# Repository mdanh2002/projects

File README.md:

# ToughDev Source Code Archive

This repository contains source code, experiments, utilities, and supporting files for projects documented on [ToughDev](https://www.toughdev.com).

I’m Minh Danh, a Singapore-based software engineer working across:

* Embedded Linux and microcontroller firmware
* C, C++, Java, Python, C#, and backend systems
* Virtualization, emulation, and retro computing
* Reverse engineering and hardware integration
* VoIP, networking, and communication systems
* AI-assisted software and data analysis

Featured work includes custom x86 and hardware emulators, QEMU experiments, embedded text-to-speech, radio and audio projects, firmware analysis, device drivers, and integrations with legacy or undocumented hardware.

The code in this repository is provided mainly as a companion to the technical articles on ToughDev. Individual projects may be experimental, hardware-specific, or preserved for reference rather than packaged as production-ready libraries.

## More Information

For project descriptions, schematics, technical investigations, build notes, and related articles, visit:

**https://www.toughdev.com**

You can also view my background and highlighted projects on the [ToughDev About page](https://www.toughdev.com/about).

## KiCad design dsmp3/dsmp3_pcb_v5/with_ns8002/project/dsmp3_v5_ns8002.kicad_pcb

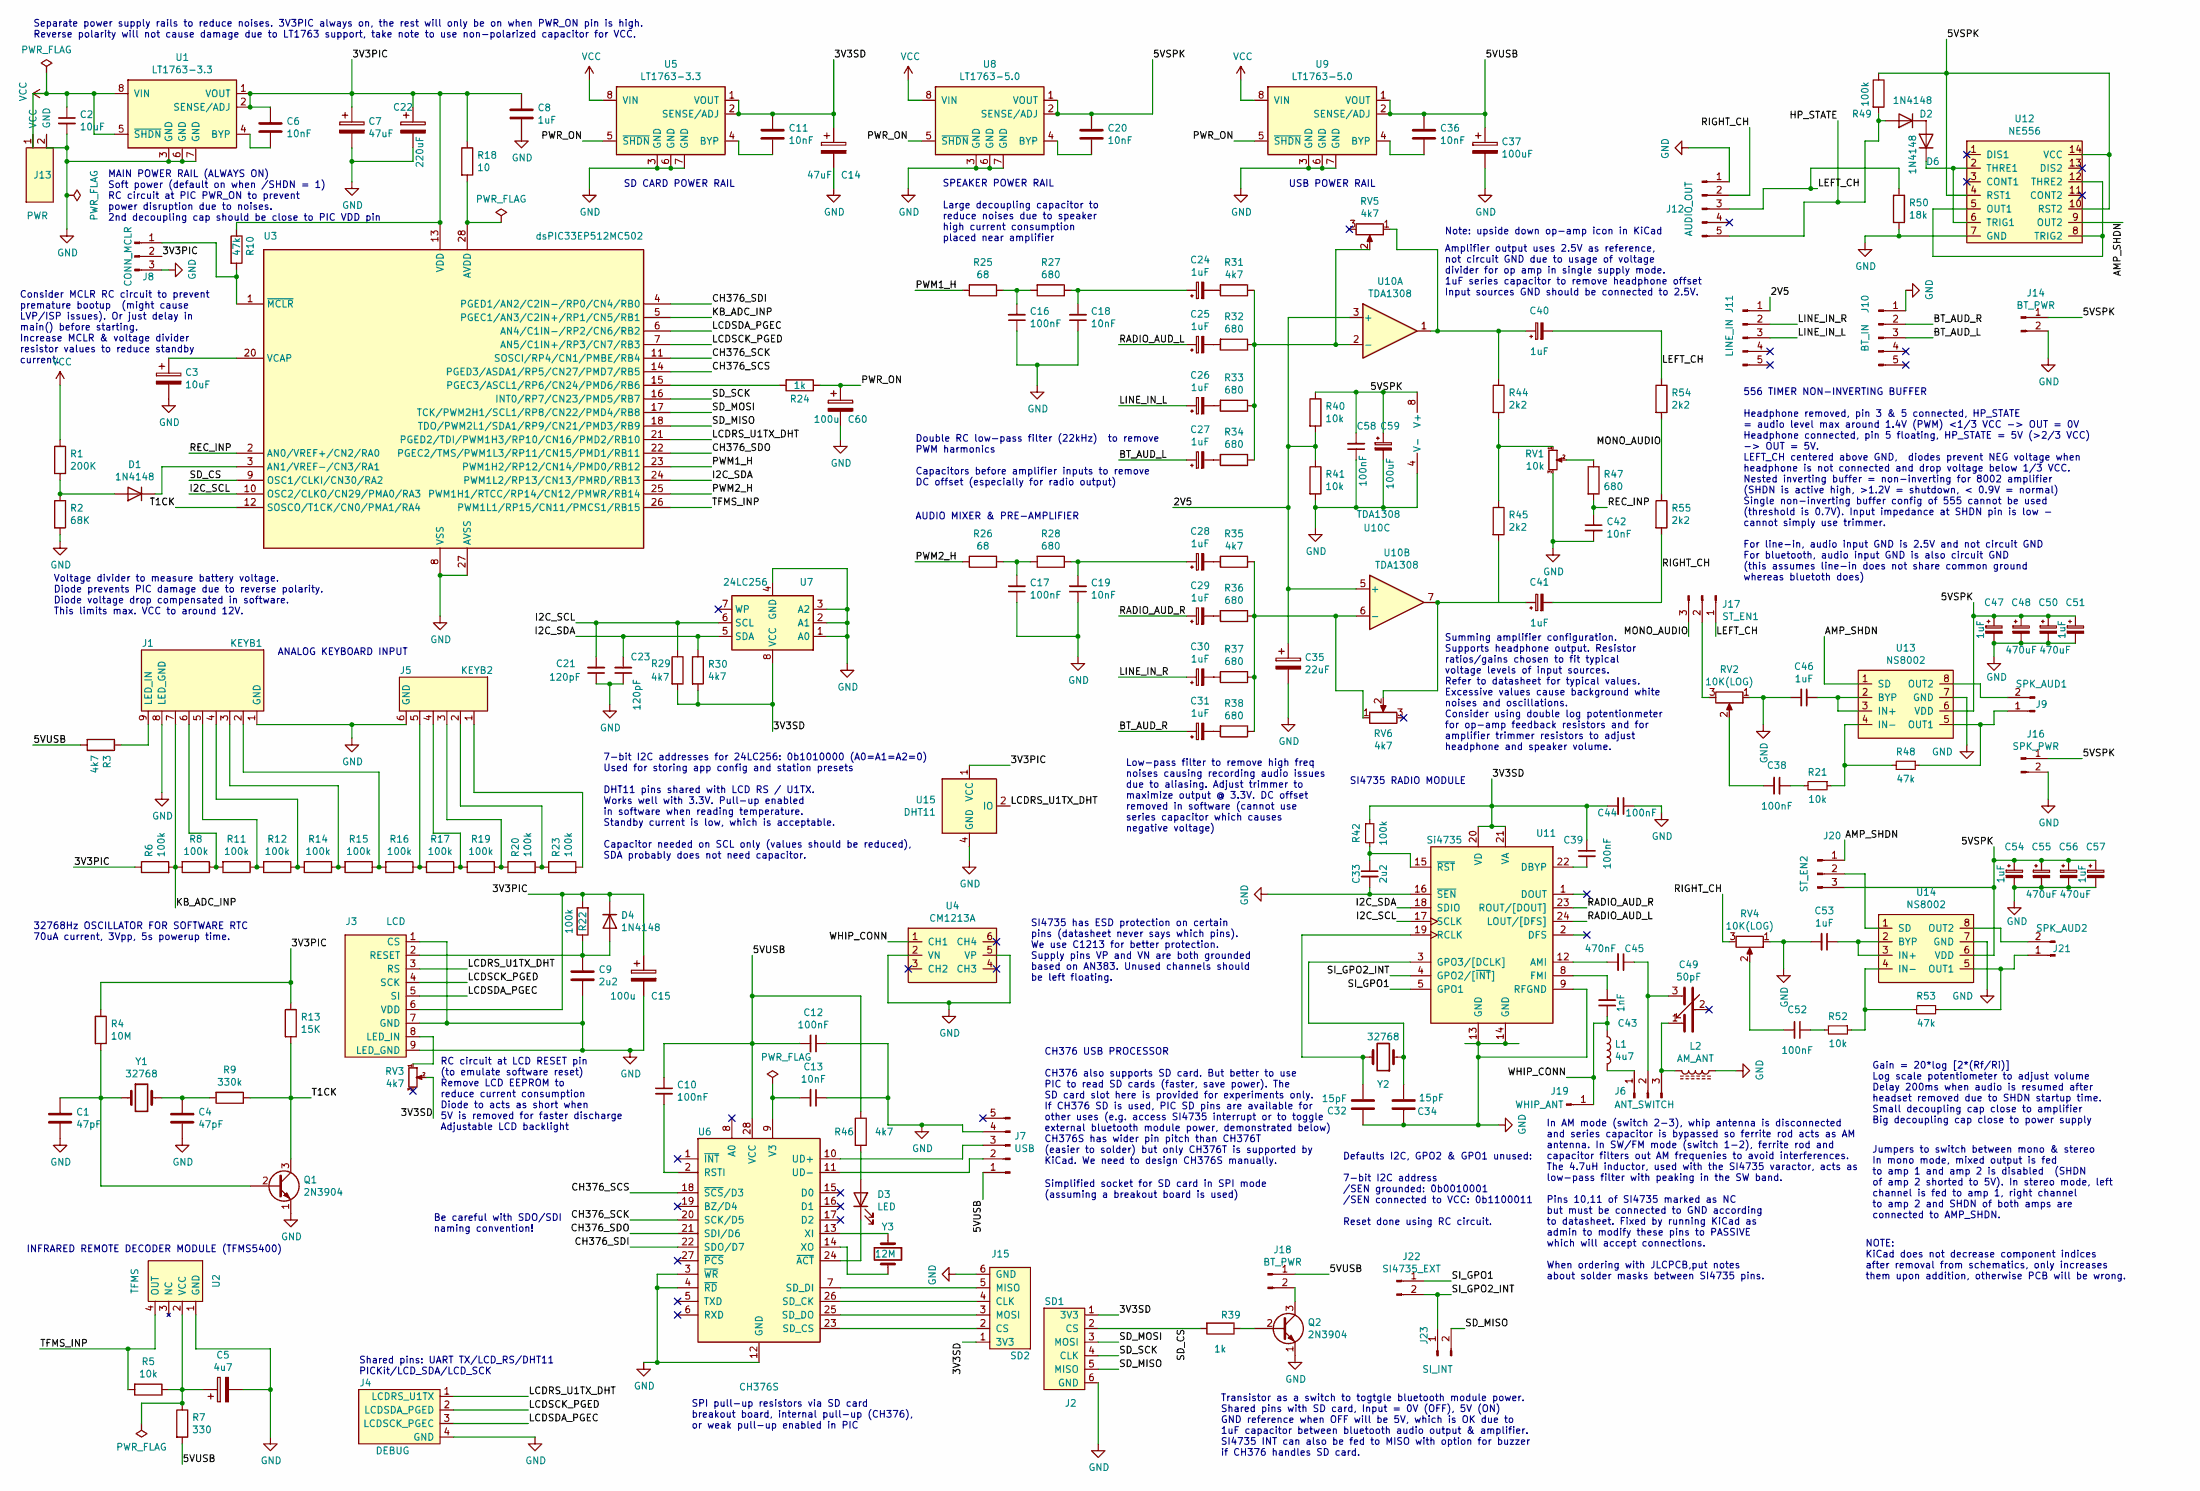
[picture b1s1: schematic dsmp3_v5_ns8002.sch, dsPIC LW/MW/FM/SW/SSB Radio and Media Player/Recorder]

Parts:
C1: 47pF; C_Disc_D3.0mm_W1.6mm_P2.50mm
C2: 10uF; C_Disc_D3.0mm_W2.0mm_P2.50mm
C3: 10uF; CP_Radial_D5.0mm_P2.50mm
C4: 47pF; C_Disc_D3.0mm_W2.0mm_P2.50mm
C5: 4u7; CP_Radial_D5.0mm_P2.50mm
C6, C11, C13, C18, C19, C20, C36, C42: 10nF; C_Disc_D3.0mm_W2.0mm_P2.50mm
C7, C14: 47uF; CP_Radial_D5.0mm_P2.50mm
C8, C24, C25, C26, C27, C28, C29, C30, C31, C40, C41: 1uF; CP_Radial_D5.0mm_P2.50mm
C9, C33: 2u2; C_Disc_D3.0mm_W2.0mm_P2.50mm
C10, C12, C16, C17, C38, C39, C44, C52, C58: 100nF; C_Disc_D3.0mm_W2.0mm_P2.50mm
C15, C60: 100u; CP_Radial_D5.0mm_P2.50mm
C21, C23: 120pF; C_Disc_D3.0mm_W2.0mm_P2.50mm
C22: 220uF; CP_Radial_D5.0mm_P2.50mm
C32, C34: 15pF; C_Disc_D3.0mm_W1.6mm_P2.50mm
C35: 22uF; CP_Radial_D5.0mm_P2.50mm
C37, C59: 100uF; CP_Radial_D5.0mm_P2.50mm
C43: 1nF; C_Disc_D3.0mm_W2.0mm_P2.50mm
C45: 470nF; C_Disc_D3.0mm_W2.0mm_P2.50mm
C46, C47, C51, C53, C54, C57: 1uF; C_Disc_D3.0mm_W2.0mm_P2.50mm
C48, C50, C55, C56: 470uF; CP_Radial_D5.0mm_P2.50mm
C49: 50pF; PinHeader_1x03_P2.54mm_Vertical
D1, D2, D4, D6: 1N4148; D_DO-35_SOD27_P7.62mm_Horizontal
D3: LED; LED_D3.0mm
J1: KEYB1; PinHeader_1x09_P2.54mm_Vertical
J2: SD1; PinHeader_1x06_P2.54mm_Vertical
J3: LCD; PinHeader_1x09_P2.54mm_Vertical
J4: DEBUG; PinHeader_1x04_P2.54mm_Vertical
J5: KEYB2; PinHeader_1x06_P2.54mm_Vertical
J6: ANT_SWITCH; PinHeader_1x03_P2.54mm_Vertical
J7: USB; USB_A_Molex_105057_Vertical
J8: CONN_MCLR; PinHeader_1x03_P2.54mm_Vertical
J9: SPK_AUD1; PinHeader_1x02_P2.54mm_Vertical
J10: BT_IN; Tayda_3.5mm_stereo_TRS_jack_A-853
J11: LINE_IN; Tayda_3.5mm_stereo_TRS_jack_A-853
J12: AUDIO_OUT; Tayda_3.5mm_stereo_TRS_jack_A-853
J13: PWR; PinHeader_1x02_P2.54mm_Vertical
J14, J18: BT_PWR; PinHeader_1x02_P2.54mm_Vertical
J15: SD2; PinHeader_1x06_P2.54mm_Vertical
J16: SPK_PWR; PinHeader_1x02_P2.54mm_Vertical
J17: ST_EN1; PinHeader_1x03_P2.54mm_Vertical
J19: WHIP_ANT; PinHeader_1x01_P2.54mm_Vertical
J20: ST_EN2; PinHeader_1x03_P2.54mm_Vertical
J21: SPK_AUD2; PinHeader_1x02_P2.54mm_Vertical
J22: SI4735_EXT; PinHeader_1x02_P2.54mm_Vertical
J23: SI_INT; PinHeader_1x02_P2.54mm_Vertical
L1: 4u7; R_Box_L8.4mm_W2.5mm_P5.08mm
L2: AM_ANT; C_Disc_D3.0mm_W2.0mm_P2.50mm
Q1, Q2: 2N3904; PinHeader_1x03_P2.54mm_Vertical
R1: 200K; R_Box_L8.4mm_W2.5mm_P5.08mm
R2: 68K; R_Box_L8.4mm_W2.5mm_P5.08mm
R3, R29, R30, R31, R35, R46: 4k7; R_Box_L8.4mm_W2.5mm_P5.08mm
R4: 10M; R_Box_L8.4mm_W2.5mm_P5.08mm
R5, R21, R40, R41, R52: 10k; R_Box_L8.4mm_W2.5mm_P5.08mm
R6, R8, R11, R12, R14, R15, R16, R17, R19, R20, R22, R23, R42, R49: 100k; R_Box_L8.4mm_W2.5mm_P5.08mm
R7: 330; R_Box_L8.4mm_W2.5mm_P5.08mm
R9: 330k; R_Box_L8.4mm_W2.5mm_P5.08mm
R10, R48, R53: 47k; R_Box_L8.4mm_W2.5mm_P5.08mm
R13: 15K; R_Box_L8.4mm_W2.5mm_P5.08mm
R18: 10; R_Box_L8.4mm_W2.5mm_P5.08mm
R24, R39: 1k; R_Box_L8.4mm_W2.5mm_P5.08mm
R25, R26: 68; R_Box_L8.4mm_W2.5mm_P5.08mm
R27, R28, R32, R33, R34, R36, R37, R38, R47: 680; R_Box_L8.4mm_W2.5mm_P5.08mm
R44, R45, R54, R55: 2k2; R_Box_L8.4mm_W2.5mm_P5.08mm
R50: 18k; R_Box_L8.4mm_W2.5mm_P5.08mm
RV1: 10k; PinHeader_1x03_P2.54mm_Vertical
RV2, RV4: 10K(LOG); PinHeader_1x03_P2.54mm_Vertical
RV3, RV5, RV6: 4k7; PinHeader_1x03_P2.54mm_Vertical
U1, U5: LT1763-3.3; SO-8_S
U2: TFMS; PinHeader_1x04_P2.54mm_Vertical
U3: dsPIC33EP512MC502; DIP-28_W7.62mm_Socket
U4: CM1213A; SOT-23-6
U6: CH376S; SOP-28_300MIL
U7: 24LC256; SOP-8_3.9x4.9mm_P1.27mm
U8, U9: LT1763-5.0; SO-8_S
U10: TDA1308; SOP-8_3.9x4.9mm_P1.27mm
U11: Si4735; SSOP-24_3.9x8.7mm_P0.635mm
U12: NE556; SO-14_3.9x8.65mm_P1.27mm
U13, U14: NS8002; SOP-8_3.9x4.9mm_P1.27mm
U15: DHT11; PinHeader_1x04_P2.54mm_Vertical
Y1, Y2: 32768; Crystal_Round_d2.0mm_Vertical
Y3: 12M; R_Box_L8.4mm_W2.5mm_P5.08mm

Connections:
/2V5: C35.1, J11.1, R40.2, R41.1, U10.3 (+), U10.5 (+)
/3V3PIC: C6.1, C7.1, C8.1, C15.1, C22.1, D4.1 (K), J3.6 (VDD), J8.2, R4.1, R6.1, R10.1, R13.1, R18.1, R22.2, U1.1 (VOUT), U1.2 (SENSE/ADJ), U3.13 (VDD), U15.1 (VCC)
/3V3SD: C11.1, C14.1, C39.2, C44.2, J2.1 (3V3), J15.1 (3V3), R29.2, R30.2, R42.1, RV3.2, U5.1 (VOUT), U5.2 (SENSE/ADJ), U7.8 (VCC), U11.20 (VD), U11.21 (VA)
/5VSPK: C20.1, C47.1, C48.1, C50.1, C51.1, C54.1, C55.1, C56.1, C57.1, C58.2, C59.1, J14.1, J16.1, J20.3, R40.1, R49.1, U8.1 (VOUT), U8.2 (SENSE/ADJ), U10.8 (V+), U12.4 (RST1), U12.10 (RST2), U12.14 (VCC), U13.6 (VDD), U14.6 (VDD)
/5VUSB: C10.1, C12.2, C36.1, C37.1, J7.1, J18.1, R3.2, R7.2, R46.1, U6.28 (VCC), U9.1 (VOUT), U9.2 (SENSE/ADJ)
/AMP_SHDN: J20.1, U12.9 (OUT2), U13.1 (SD)
/BT_AUD_L: C27.1, J10.3
/BT_AUD_R: C31.1, J10.2
/CH376_SCK: U3.11 (SOSCI/RP4/CN1/PMBE/RB4), U6.20 (SCK/D5)
/CH376_SCS: U3.14 (PGED3/ASDA1/RP5/CN27/PMD7/RB5), U6.18 (~SCS~/D3)
/CH376_SDI: U3.4 (PGED1/AN2/C2IN-/RP0/CN4/RB0), U6.22 (SDO/D7)
/CH376_SDO: U3.22 (PGEC2/TMS/PWM1L3/RP11/CN15/PMD1/RB11), U6.21 (SDI/D6)
/HP_STATE: D2.2 (A), J12.5, R49.2
/I2C_SCL: C21.2, R29.1, U3.10 (OSC2/CLKO/CN29/PMA0/RA3), U7.6 (SCL), U11.17 (SCLK)
/I2C_SDA: C23.2, R30.1, U3.24 (PWM1L2/RP13/CN13/PMRD/RB13), U7.5 (SDA), U11.18 (SDIO)
/KB_ADC_INP: J1.7, R6.2, R8.2, U3.5 (PGEC1/AN3/C2IN+/RP1/CN5/RB1)
/LCDRS_U1TX_DHT: J3.3 (RS), J4.1 (LCDRS_U1TX), U3.21 (PGED2/TDI/PWM1H3/RP10/CN16/PMD2/RB10), U15.2 (IO)
/LCDSCK_PGED: J3.4 (SCK), J4.2 (LCDSDA_PGED), U3.7 (AN5/C1IN+/RP3/CN7/RB3)
/LCDSDA_PGEC: J3.5 (SI), J4.3 (LCDSCK_PGEC), U3.6 (AN4/C1IN-/RP2/CN6/RB2)
/LEFT_CH: C40.2, J12.3, J17.1, R50.1, R54.1
/LINE_IN_L: C26.1, J11.3
/LINE_IN_R: C30.1, J11.2
/MONO_AUDIO: J17.3, R54.2, R55.1
/PWM1_H: R25.2, U3.23 (PWM1H2/RP12/CN14/PMD0/RB12)
/PWM2_H: R26.2, U3.25 (PWM1H1/RTCC/RP14/CN12/PMWR/RB14)
/PWR_ON: C60.1, R24.1, U5.5 (~SHDN), U8.5 (~SHDN), U9.5 (~SHDN)
/RADIO_AUD_L: C25.1, U11.24 (LOUT/[DFS])
/RADIO_AUD_R: C29.1, U11.23 (ROUT/[DOUT])
/REC_INP: C42.1, R47.2, U3.2 (AN0/VREF+/CN2/RA0)
/RIGHT_CH: C41.2, J12.2, R55.2, RV4.3
/SD_CS: J2.2 (CS), R39.2, U3.9 (OSC1/CLKI/CN30/RA2)
/SD_MISO: J2.5 (MISO), J23.2, U3.18 (TDO/PWM2L1/SDA1/RP9/CN21/PMD3/RB9)
/SD_MOSI: J2.3 (MOSI), U3.17 (TCK/PWM2H1/SCL1/RP8/CN22/PMD4/RB8)
/SD_SCK: J2.4 (CLK), U3.16 (INT0/RP7/CN23/PMD5/RB7)
/SI_GPO1: J22.1, U11.5 (GPO1)
/SI_GPO2_INT: J22.2, J23.1, U11.4 (GPO2/[~INT~])
/T1CK: Q1.3 (C), R9.1, R13.2, U3.12 (SOSCO/T1CK/CN0/PMA1/RA4)
/TFMS_INP: R5.2, U2.4 (OUT), U3.26 (PWM1L1/RP15/CN11/PMCS1/RB15)
/WHIP_CONN: C43.1, J19.1, L1.1, U4.1 (CH1)
GND: C1.2, C2.2, C3.2, C4.2, C5.2, C7.2, C8.2, C9.1, C12.1, C13.1, C14.2, C15.2, C16.1, C17.1, C18.1, C19.1, C21.1, C22.2, C23.1, C32.1, C33.2, C34.1, C35.2, C37.2, C42.2, C44.1, C46.2, C47.2, C48.2, C50.2, C51.2, C53.2, C54.2, C55.2, C56.2, C57.2, C58.1, C59.2, C60.2, J1.1 (GND), J1.8 (LED_GND), J2.6 (GND), J3.1 (CS), J3.7 (GND), J3.9 (LED_GND), J4.4 (GND), J5.6 (GND), J7.4, J8.3, J10.1, J12.1, J13.2 (GND), J14.2, J15.6 (GND), J16.2, L2.1, Q1.1 (E), Q2.1 (E), R2.2, R41.2, R50.2, RV1.3, RV2.1, RV4.1, U1.3 (GND), U1.6 (GND), U1.7 (GND), U2.1 (GND), U3.8 (VSS), U3.19 (VSS), U3.27 (AVSS), U4.2 (VN), U4.5 (VP), U5.3 (GND), U5.6 (GND), U5.7 (GND), U6.3 (~WR~), U6.4 (~RD~), U6.12 (GND), U7.1 (A0), U7.2 (A1), U7.3 (A2), U7.4 (GND), U8.3 (GND), U8.6 (GND), U8.7 (GND), U9.3 (GND), U9.6 (GND), U9.7 (GND), U10.4 (V-), U11.9 (RFGND), U11.10 (NC), U11.11 (NC), U11.13 (GND), U11.14 (GND), U11.16 (~SEN), U12.7 (GND), U13.7 (GND), U14.7 (GND), U15.4 (GND)
unnamed: C1.1, Q1.2 (B), R4.2, Y1.1
unnamed: C3.1, U3.20 (VCAP)
unnamed: C4.1, R9.2, Y1.2
unnamed: C5.1, R5.1, R7.1, U2.2 (VCC)
unnamed: C6.2, U1.4 (BYP)
unnamed: C9.2, D4.2 (A), J3.2 (RESET), R22.1
unnamed: C10.2, U6.2 (RSTI)
unnamed: C11.2, U5.4 (BYP)
unnamed: C13.2, U6.9 (V3)
unnamed: C16.2, R25.1, R27.2
unnamed: C17.2, R26.1, R28.2
unnamed: C18.2, C24.1, R27.1
unnamed: C19.2, C28.1, R28.1
unnamed: C20.2, U8.4 (BYP)
unnamed: C24.2, R31.2
unnamed: C25.2, R32.2
unnamed: C26.2, R33.2
unnamed: C27.2, R34.2
unnamed: C28.2, R35.2
unnamed: C29.2, R36.2
unnamed: C30.2, R37.2
unnamed: C31.2, R38.2
unnamed: C32.2, U11.19 (RCLK), Y2.2
unnamed: C33.1, R42.2, U11.15 (~RST)
unnamed: C34.2, U11.3 (GPO3/[DCLK]), Y2.1
unnamed: C36.2, U9.4 (BYP)
unnamed: C38.1, R21.2
unnamed: C38.2, RV2.2
unnamed: C39.1, U11.22 (DBYP)
unnamed: C40.1, R44.1, RV5.1, U10.1
unnamed: C41.1, R45.2, RV6.2, U10.7
unnamed: C43.2, U11.8 (FMI)
unnamed: C45.1, C49.3, J6.2
unnamed: C45.2, U11.12 (AMI)
unnamed: C46.1, U13.2 (BYP), U13.3 (IN+)
unnamed: C49.1, J6.3, L2.2
unnamed: C52.1, R52.2
unnamed: C52.2, RV4.2
unnamed: C53.1, U14.2 (BYP), U14.3 (IN+)
unnamed: D1.1 (K), U3.3 (AN1/VREF-/CN3/RA1)
unnamed: D1.2 (A), R1.2, R2.1
unnamed: D2.1 (K), D6.2 (A)
unnamed: D3.1 (K), U6.24 (~ACT~)
unnamed: D3.2 (A), R46.2
unnamed: D6.1 (K), U12.2 (THRE1), U12.6 (TRIG1)
unnamed: J1.2, R15.1, R16.2
unnamed: J1.3, R14.1, R15.2
unnamed: J1.4, R12.1, R14.2
unnamed: J1.5, R11.1, R12.2
unnamed: J1.6, R8.1, R11.2
unnamed: J1.9 (LED_IN), R3.1
unnamed: J3.8 (LED_IN), RV3.1
unnamed: J5.1, R23.2
unnamed: J5.2, R20.2, R23.1
unnamed: J5.3, R19.1, R20.1
unnamed: J5.4, R17.1, R19.2
unnamed: J5.5, R16.1, R17.2
unnamed: J6.1, L1.2
unnamed: J7.2, U6.11 (UD-)
unnamed: J7.3, U6.10 (UD+)
unnamed: J8.1, R10.2, U3.1 (~MCLR)
unnamed: J9.1, R48.1, U13.5 (OUT1)
unnamed: J9.2, U13.8 (OUT2)
unnamed: J15.2 (CS), U6.23 (SD_CS)
unnamed: J15.3 (MOSI), U6.25 (SD_DO)
unnamed: J15.4 (CLK), U6.26 (SD_CK)
unnamed: J15.5 (MISO), U6.7 (SD_DI)
unnamed: J17.2, RV2.3
unnamed: J18.2, Q2.3 (C)
unnamed: J20.2, U14.1 (SD)
unnamed: J21.1, R53.1, U14.5 (OUT1)
unnamed: J21.2, U14.8 (OUT2)
unnamed: Q2.2 (B), R39.1
unnamed: R18.2, U3.28 (AVDD)
unnamed: R21.1, R48.2, U13.4 (IN-)
unnamed: R24.2, U3.15 (PGEC3/ASCL1/RP6/CN24/PMD6/RB6)
unnamed: R31.1, R32.1, R33.1, R34.1, RV5.2, U10.2 (-)
unnamed: R35.1, R36.1, R37.1, R38.1, RV6.1, U10.6 (-)
unnamed: R44.2, R45.1, RV1.1
unnamed: R47.1, RV1.2
unnamed: R52.1, R53.2, U14.4 (IN-)
unnamed: U6.13 (XI), Y3.1
unnamed: U6.14 (XO), Y3.2
unnamed: U12.5 (OUT1), U12.8 (TRIG2), U12.12 (THRE2)
VCC: C2.1, J13.1 (VCC), R1.1, U1.5 (~SHDN), U1.8 (VIN), U5.8 (VIN), U8.8 (VIN), U9.8 (VIN)

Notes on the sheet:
Consider MCLR RC circuit to prevent premature bootup (might cause LVP/ISP issues). Or just delay in main() before starting. Increase MCLR & voltage divider resistor values to reduce standby current.
Amplifier output uses 2.5V as reference, not circuit GND due to usage of voltage divider for op amp in single supply mode. 1uF series capacitor to remove headphone offset Input sources GND should be connected to 2.5V.
MAIN POWER RAIL (ALWAYS ON) Soft power (default on when /SHDN = 1) RC circuit at PIC PWR_ON to prevent power disruption due to noises. 2nd decoupling cap should be close to PIC VDD pin
32768Hz OSCILLATOR FOR SOFTWARE RTC 70uA current, 3Vpp, 5s powerup time.
Shared pins: UART TX/LCD_RS/DHT11 PICKit/LCD_SDA/LCD_SCK
INFRARED REMOTE DECODER MODULE (TFMS5400)
ANALOG KEYBOARD INPUT
Summing amplifier configuration. Supports headphone output. Resistor ratios/gains chosen to fit typical voltage levels of input sources. Refer to datasheet for typical values. Excessive values cause background white noises and oscillations. Consider using double log potentionmeter for op-amp feedba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
Double RC low-pass filter (22kHz) to remove PWM harmonics Capacitors before amplifier inputs to remove DC offset (especially for radio output)
Low-pass filter to remove high freq noises causing recording audio issues due to aliasing. Adjust trimmer to maximize output @ 3.3V. DC offset removed in software (cannot use series capacitor which causes negative voltage)
SPEAKER POWER RAIL Large decoupling capacitor to reduce noises due to speaker high current consumption placed near amplifier
Separate power supply rails to reduce noises. 3V3PIC always on, the rest will only be on when PWR_ON pin is high. Reverse polarity will not cause damage due to LT1763 support, take note to use non-polarized capacitor for VCC.
556 TIMER NON-INVERTING BUFFER Headphone removed, pin 3 & 5 connected, HP_STATE = audio level max around 1.4V (PWM) <1/3 VCC -> OUT = 0V Headphone connected, pin 5 floating, HP_STATE = 5V (>2/3 VCC) -> OUT = 5V. LEFT_CH centered above GND, diodes prevent NEG voltage when headphone is not connected 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
SD CARD POWER RAIL
Voltage divider to measure battery voltage. Diode prevents PIC damage due to reverse polarity. Diode voltage drop compensated in software. This limits max. VCC to around 12V.
For line-in, audio input GND is 2.5V and not circuit GND For bluetooth, audio input GND is also circuit GND (this assumes line-in does not share common ground whereas bluetoth does)
AUDIO MIXER & PRE-AMPLIFIER
USB POWER RAIL
Gain = 20*log [2*(Rf/Ri)] Log scale potentiometer to adjust volume Delay 200ms when audio is resumed after headset removed due to SHDN startup time. Small decoupling cap close to amplifier Big decoupling cap close to power supply
CH376 USB PROCESSOR CH376 also supports SD card. But better to use PIC to read SD cards (faster, save power). The SD card slot here is provided for experiments only. If CH376 SD is used, PIC SD pins are available for other uses (e.g. access SI4735 interrupt or to toggle external bluetooth module po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
Simplified socket for SD card in SPI mode (assuming a breakout board is used)
Note: upside down op-amp icon in KiCad
SPI pull-up resistors via SD card breakout board, internal pull-up (CH376), or weak pull-up enabled in PIC
7-bit I2C addresses for 24LC256: 0b1010000 (A0=A1=A2=0) Used for storing app config and station presets DHT11 pins shared with LCD RS / U1TX. Works well with 3.3V. Pull-up enabled in software when reading temperature. Standby current is low, which is acceptable. Capacitor needed on SCL only (values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
RC circuit at LCD RESET pin (to emulate software reset) Remove LCD EEPROM to reduce current consumption Diode to acts as short when 5V is removed for faster discharge Adjustable LCD backlight
Be careful with SDO/SDI naming convention!
Jumpers to switch between mono & stereo In mono mode, mixed output is fed to amp 1 and amp 2 is disabled (SHDN of amp 2 shorted to 5V). In stereo mode, left channel is fed to amp 1, right channel to amp 2 and SHDN of both amps are connected to AMP_SHDN.
NOTE: KiCad does not decrease component indices after removal from schematics, only increases them upon addition, otherwise PCB will be wrong.
Transistor as a switch to togtgle bluetooth module power. Shared pins with SD card, Input = 0V (OFF), 5V (ON) GND reference when OFF will be 5V, which is OK due to 1uF capacitor between bluetooth audio output & amplifier. SI4735 INT can also be fed to MISO with option for buzzer if CH376 handles SD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
SI4735 has ESD protection on certain pins (datasheet never says which pins). We use C1213 for better protection. Supply pins VP and VN are both grounded based on AN383. Unused channels should be left floating.
In AM mode (switch 2-3), whip antenna is disconnected and series capacitor is bypassed so ferrite rod acts as AM antenna. In SW/FM mode (switch 1-2), ferrite rod and capacitor filters out AM frequenies to avoid interferences. The 4.7uH inductor, used with the SI4735 varactor, acts as low-pass filte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
Defaults I2C, GPO2 & GPO1 unused: 7-bit I2C address /SEN grounded: 0b0010001 /SEN connected to VCC: 0b1100011 Reset done using RC circuit.
SI4735 RADIO MODULE

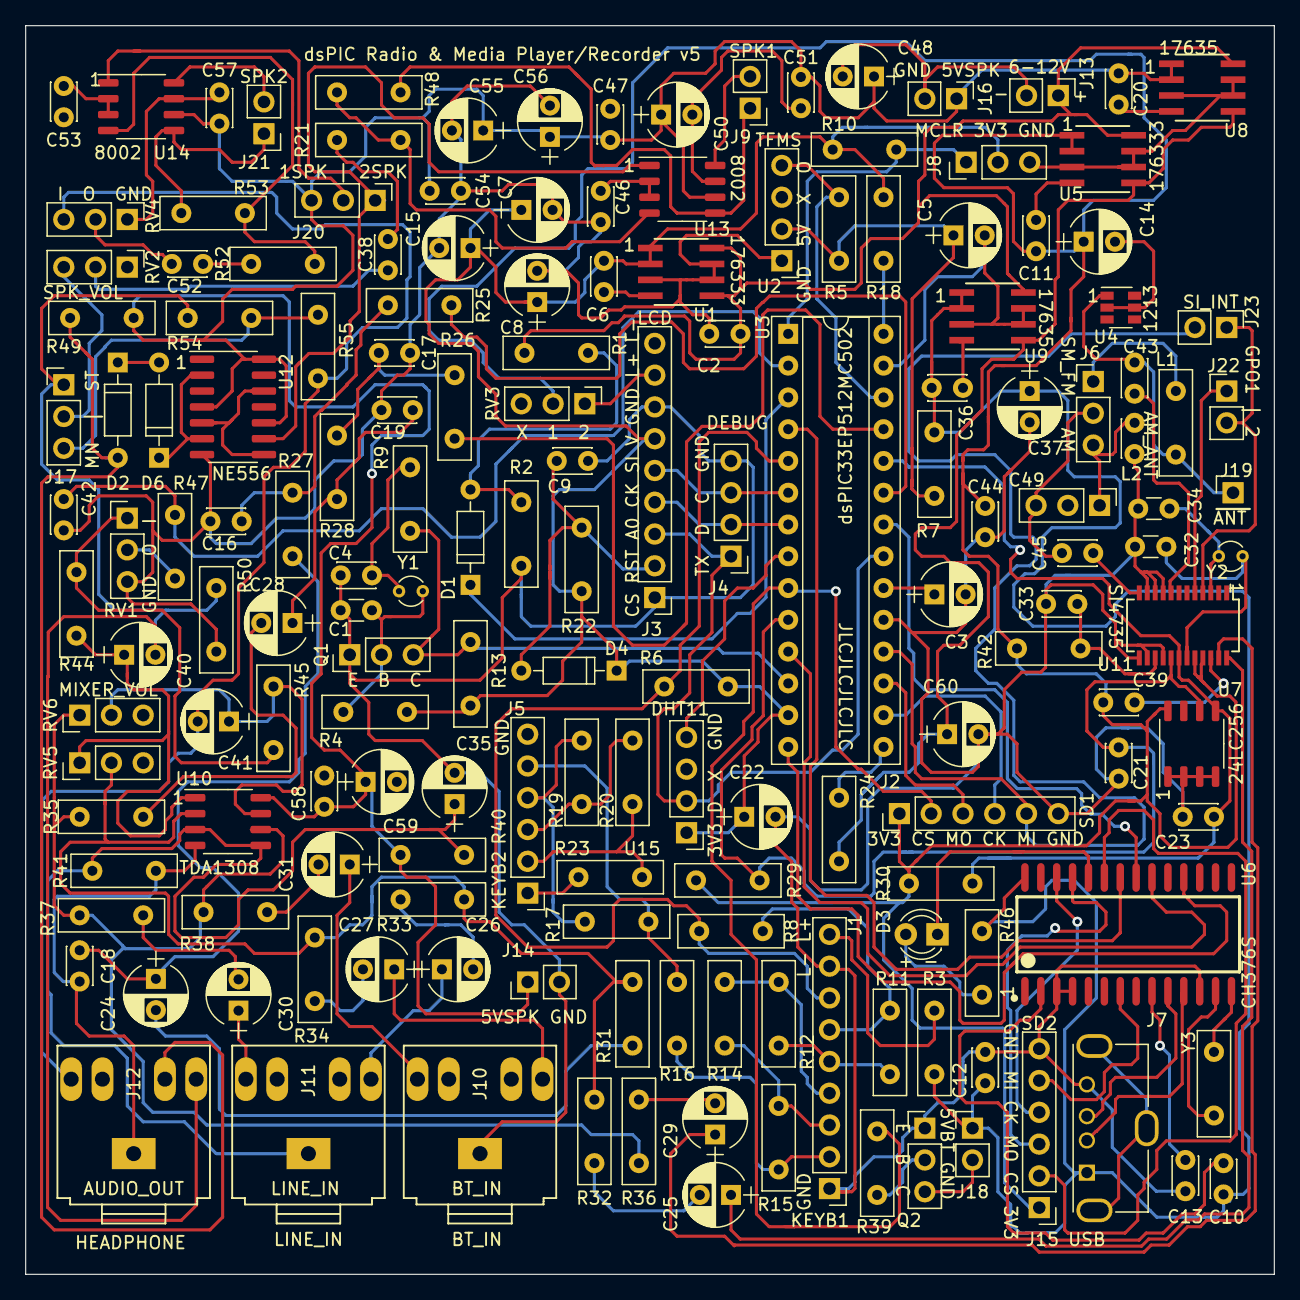
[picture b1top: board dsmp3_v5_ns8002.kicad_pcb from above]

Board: 2 copper layers, 99.8 x 99.8 mm, 169 parts (0 on the bottom side), 125 nets.
